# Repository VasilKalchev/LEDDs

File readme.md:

<p align=center>trailing-edge dimmer for LED bulbs</p>

<div align=center>

</div>

**LEDDs** is an open-source hardware, DIY, smart dimmer for 230 V LED bulbs. It is built around the ESP32-C3-12F and is designed to sit on a desk or table, replacing standard inline cord switches.

The project consists of a **PCB**, a **3D-printable chassis**, and a **top plate** designed as a PCB. It runs [ESPHome](https://esphome.io) for integration with Home Assistant and features a **rotary encoder** so it can be controlled easily or used as a standalone device.

> [!CAUTION]
> **MAINS VOLTAGE:** This device operates at **230 VAC**. Touching live components can result in serious injury or death.
> * Only build if you have relevant experience with high-voltage electronics.
> * Always unplug before opening!
> * While the design includes safety features (fuse, MOVs), it is not a certified design and should be treated with caution.

## Table of contents
* [Is this project for you?](#is-this-project-for-you)
* [Why trailing-edge?](#why-trailing-edge)
* [Features](#star-features)
* [Specifications](#straight_ruler-specifications)
* [Release/fabrication of version 2.0](#releasefabrication-of-v20)
* [Repository structure](#open_file_folder-repository-structure)
* [Bill of materials](#euro-bill-of-materials)
* [Build](#hammer-build)
   * [Prerequisites](#prerequisites)
   * [1. Ordering the components](#1-ordering-the-components)
   * [2. PCB assembly instructions](#2-pcb-assembly-instructions)
   * [3. Flashing the firmware](#3-flashing-the-firmware)
   * [4. Preparing the enclosure](#4-preparing-the-enclosure)
   * [5. Final assembly](#5-final-assembly)
* [Usage](#bulb-usage)
   * [Control](#control)
   * [LED indicators](#led-indicators)
   * [Default light effects](#default-light-effects)
* [Versions, releases and compatibility](#page_with_curl-versions-releases-and-compatibility)
* [Contributing](#coffee-contributing)
* [License](#license)

---

## Is this project for you?
This project is suitable if you:
 - have experience with mains-powered electronics
 - want a LED bulbs dimmer for a desk

This project is NOT suitable if you:
 - are new to electronics
 - need a certified wall dimmer

## Why trailing-edge?
Most dimmers use **leading-edge** (TRIAC) dimming (designed for incandescent bulbs). They modulate power to the load by cutting the beginning of the AC half cycle. This creates a voltage spike that can cause buzzing and reduced lifespan in the capacitive power supplies found in LED bulbs.

**LEDDs uses trailing-edge dimming.** By using MOSFETs to cut the waveform at the *end* of the AC cycle, there isn't a positive voltage spike. This results in:
* reduced electrical noise and buzzing
* smoother dimming with reduced flicker
* lower minimum brightness levels

> The schematic and PCB can be viewed in [KiCanvas][kicanvas_v2_0].

## :star: Features
- **ESP32-C3** based with ESPHome firmware for integration with Home Assistant
- **Standalone** operation, doesn't require Home Assistant
- **Rotary encoder** control: rotate to dim, press+rotate for effects, press for on/off
- LEDs: red (rotation feedback), blue (status indicator), white (ambient)
- Included **enclosure design**: 100 mm × 51 mm × 25 mm - ideal for desk lamp modifications
- Low idle power: ~0.3 W
- Open source: MIT licensed

## :straight_ruler: Specifications

| Parameter              | Value                        |
| ---------------------- | ---------------------------- |
| Input voltage          | 230 VAC                      |
| Maximum output power   | 100 W                        |
| Idle power draw        | ~0.3 W                       |
| Protections            | fuse and MOVs                |
| Microcontroller module | ESP32-C3-12F [^1]            |
| Dimensions             | 100 × 51 × 25 mm (W × D × H) |
| Connectivity           | Wi-Fi, USB-C (programming)   |

[^1]: Also compatible with ESP8266 ESP-12F, but not recommended.

> [!IMPORTANT]
> Designed for 230 VAC at 50 Hz.
>
> Usage with 120 VAC at 60 Hz will probably require adjusting the component values of the zero-cross and the voltage regulator circuits.

---

## Release/fabrication of v2.0

> **Status:** Verified working.
> The fabricated board from this release is fully functional. Minor issues may exist but do not affect operation: [/doc/releaselog.md v2.0][releaselog_v2_0].
>
> :memo: **Recommended for fabrication.**

<p align="center">

</p>

---

## :open_file_folder: Repository structure
```

├── hw/                       # main PCB design (KiCad project)
│   ├── lib/                  # symbols and footprints
│   ├── assets/               # fonts and graphics
│   └── export/               # scripts for exporting gerbers, BOM and schematics/PCB PDFs
├── fw/                       # ESPHome YAML configurations and firmware binaries
├── doc/                      # additional documentation
│   ├── releaselog.md         # main PCB release log
│   ├── changelog.md          # main PCB change log
├── enclosure/
│   ├── chassis/              # 3D printable chassis
│   │   ├── releaselog.md     # chassis release log
│   │   ├── changelog.md      # chassis change log
│   │   ├── vX.Y-variant_a/
│   │   └── vX.Y-variant_b/
│   └── top_plate/            # top plate design (KiCad project)
│       ├── releaselog.md     # top plate release log
│       ├── changelog.md      # top plate change log
│       ├── vX.Y-variant_a/
│       └── vX.Y-variant_b/
└── img/                      # photos and renders
```

---

## :euro: Bill of materials
 - components: ~€15
 - PCB: €4 (ordered as prototype board)
 - top plate: €0-4 (can be combined with the main PCB)
 - chassis: €4-10 (when ordered)

Check out the BOM provided in the release bundle for complete components list.

## :hammer: Build

### Overview
Building LEDDs consists of four main steps:
 1. Ordering the PCB, the chassis and the components.
 2. Assembling the PCB.
 3. Flashing and configuring the firmware.
 4. Wiring and final assembly.

### Prerequisites
- skills: soldering [^2], experience with mains electricity
- tools: soldering iron, hot air gun (recommended), 3D printer or access to 3D printing service, multimeter

[^2]: Trickiest part is the USB-C port. The board can be ordered pre-assembled.

Download the [release bundle][dw_release_bundle_v2_0].

### 1. Ordering the components
  - **PCBs**: order the main PCB and the top plate PCB from your preferred fabricator
    - gerbers for JLCPCB: available in the bundle
    - for other fabricators - use KiCad to generate gerbers according to the manufacturer's instructions
  - **chassis**: choose a variant from the provided STL files

### 2. PCB assembly instructions
> [!TIP]
> Use the provided **interactive BOM** ("ibom.html") as a soldering guide.

#### Microcontroller module
<strong>ESP32-C3-12F (recommended)</strong>

- solder R13

<details><summary><strong>ESP8266 ESP-12F (not recommended)</strong></summary>

- insulate pins 12 and 13 from the PCB pads using kapton/electrical tape
- solder JP2
- don't solder R13
- don't solder R6 and D3 ("led_1")
- don't solder R8 and D5 ("led_3")

ESP8266 doesn't support native USB and requires an external USB to serial adapter for programming.

</details>

#### Zero-cross optoisolator
The PCB has footprints for a choice between 2 optoisolators that connect the zero-cross signal to the MCU.

<strong>H11L1SR2M</strong>

 - solder the optoisolator on footprint U4
 - solder C13

<details><summary><strong>PC817XI (not recommended)</strong></summary>

- solder the optoisolator on footprint U3
- no need to solder C13

This optoisolator is the same as the one used for controlling the MOSFET's gate, but didn't work well for the zero-cross circuit.

</details>

#### Skipping the relay
The relay is used to power off the mains part of the circuit when the load is turned off. This is intended as a peace of mind feature and can be omitted.

 - use a wire to short pin 11 to 14
 - use a wire to short pin 21 to 24
 - no need to solder C3, D2, R2 and Q1

#### Skipping the rotary encoder

If the rotary encoder is not required - solder a push button (SW2) so boot mode can be entered manually.

 - no need to solder R3, R4, C4, C5 and C6

A modified top plate (without a hole in the middle) is recommended for safety reasons (not currently available).

#### Using the UART header instead of the USB for programming *(not tested)*

 - solder R12
 - solder header J4
 - no need to solder R9 and R10

Use a USB to serial adapter.

### 3. Flashing the firmware
 - Connect to the board via USB-C.
 - Use [ESPHome's web flasher](https://web.esphome.io/) to upload one of the provided firmware binaries.
   - hass.bin: Home Assistant + rotary encoder
   - web_server.bin: self hosted web server + rotary encoder
   - standalone: rotary encoder only
 - Set your Wi-Fi credentials using the ESPHome web flasher.
 - Test before wiring.

> [!TIP]
> The YAML configurations of the provided binaries are available under [/fw/esphome/yaml/](/fw/esphome/yaml/).

### 4. Preparing the enclosure
- plastic chassis: install the heat-set threaded inserts in the holes using a soldering iron
- resin chassis: no preparation needed

### 5. Final assembly
 - Mount a knob to the rotary encoder.
 - Place the PCB inside the chassis.
 - Screw the mains power cable to the terminal on the left (marked with a power plug). **Don't connect power until fully assembled.**
 - Screw the lamp socket cable to the terminal on the right (marked with a bulb).
 - Pass the screws through the top plate and place the spacers on the screws.
 - Screw the top plate through the PCB into the chassis.

## :bulb: Usage
### Control
**Directly** *(possible with all firmware variants)*:
 - **press**: on/off
 - **rotate**: brightness adjustment
 - **press + rotate**: cycle lighting effects

**Home Assistant** *(included in hass.bin)*:

Integrating the device in Home Assistant: https://esphome.io/guides/getting_started_hassio/#connecting-your-device-to-home-assistant.

The "Configuration" section allows customization of the device:
 - **Bulb power rating**: input the power rating of the bulb, this is used for the power estimation sensor ("Power \[est\]").
 - **Gamma correct**: Adjust the dimming curve to appear linear to the human eye.
 - **Minimum level**: The lowest level at which the bulb emits light. *Note: this value needs to be updated every time gamma correction is changed.*
 - **Restore mode**: Initial state of the bulb when powered.
 - **Transition length**: How fast the bulb changes brightness in milliseconds.
 - **LED: red/blue/white**: set the ambient brightness of the LEDs.

**Web server** *(included in web_server.bin)*:
> This is useful if you don't have Home Assistant, but want to control the device remotely.

### LED indicators
There are three LEDs on the board:
 - **red (top, led_1):** ambient / rotation feedback
 - **blue (top, led_2):** ambient / status indicator
 - **white (bottom, led_3):** ambient

### Default light effects
Light effects can be cycled with the rotary encoder or chosen directly from a UI.

 - Pulse (low, fast)
 - Pulse (low, slow)
 - Pulse (high, fast)
 - Pulse (high, slow)
 - Pulse (full, fast)
 - Pulse (full, slow)
 - Flicker (soft)
 - Flicker (intense)

<!--
<div>

</div>
-->

## :page_with_curl: Versions, releases and compatibility
Each fabrication run results in a **GitHub release**.
- Semantic versioning (major.minor), no patch versions.
- PCB, chassis, and top plate are versioned independently.
- Same **major versions fit together**.

## :coffee: Contributing
Every type of contribution is welcome, like improvements or corrections to the:
- schematic/PCB design
- documentation
- enclosure (chassis and top panel) design
- ESPHome configuration

Contributions can be made as improvements or as variants (e.g. different enclosure design, ESPHome configuration, etc.).

```mermaid
gitGraph
    commit tag: "v1.0"
    branch improve_x
    checkout improve_x
    commit id: "Improve x"
    commit id: "Re-generate exports"
    commit id: "Update board documentation"
    checkout main
    merge improve_x tag: "v1.1"
    branch replace_y
    checkout replace_y
    commit id: "Replace y"
    commit id: "Generate exports"
    commit id: "Compile binaries"
    commit id: "Update all documentation"
    checkout main
    merge replace_y tag: "v2.0"
```

You're welcome to post your builds in [Discussions: Show and tell](https://github.com/VasilKalchev/LEDDs/discussions/categories/show-and-tell).

## License
This project is licensed under the **MIT License**.

---

**Disclaimer**: This project involves mains voltage electricity. The author assumes no liability for injury, damage, or regulatory violations. Build and use at your own risk. Ensure compliance with local electrical codes and regulations.

<!-- current version links -->

[kicanvas_v2_0]: https://kicanvas.org/?github=https%3A%2F%2Fgithub.com%2FVasilKalchev%2FLEDDs%2Ftree%2Fv2.0%2Fhw
[dw_release_bundle_v2_0]: https://github.com/VasilKalchev/LEDDs/releases/download/v2.0/LEDDs.v2.0.zip

[releaselog_v2_0]: /doc/releaselog.md#v20---2025-04-02

<!-- /current version links -->

<!-- checklist
<details>
<summary>/readme.md checklist</summary>

 - [x] set release result (template in releaselog.md)
 - [x] update the sections as needed
 - [x] comment out this checklist

</details>

-->
<!-- /checklist -->

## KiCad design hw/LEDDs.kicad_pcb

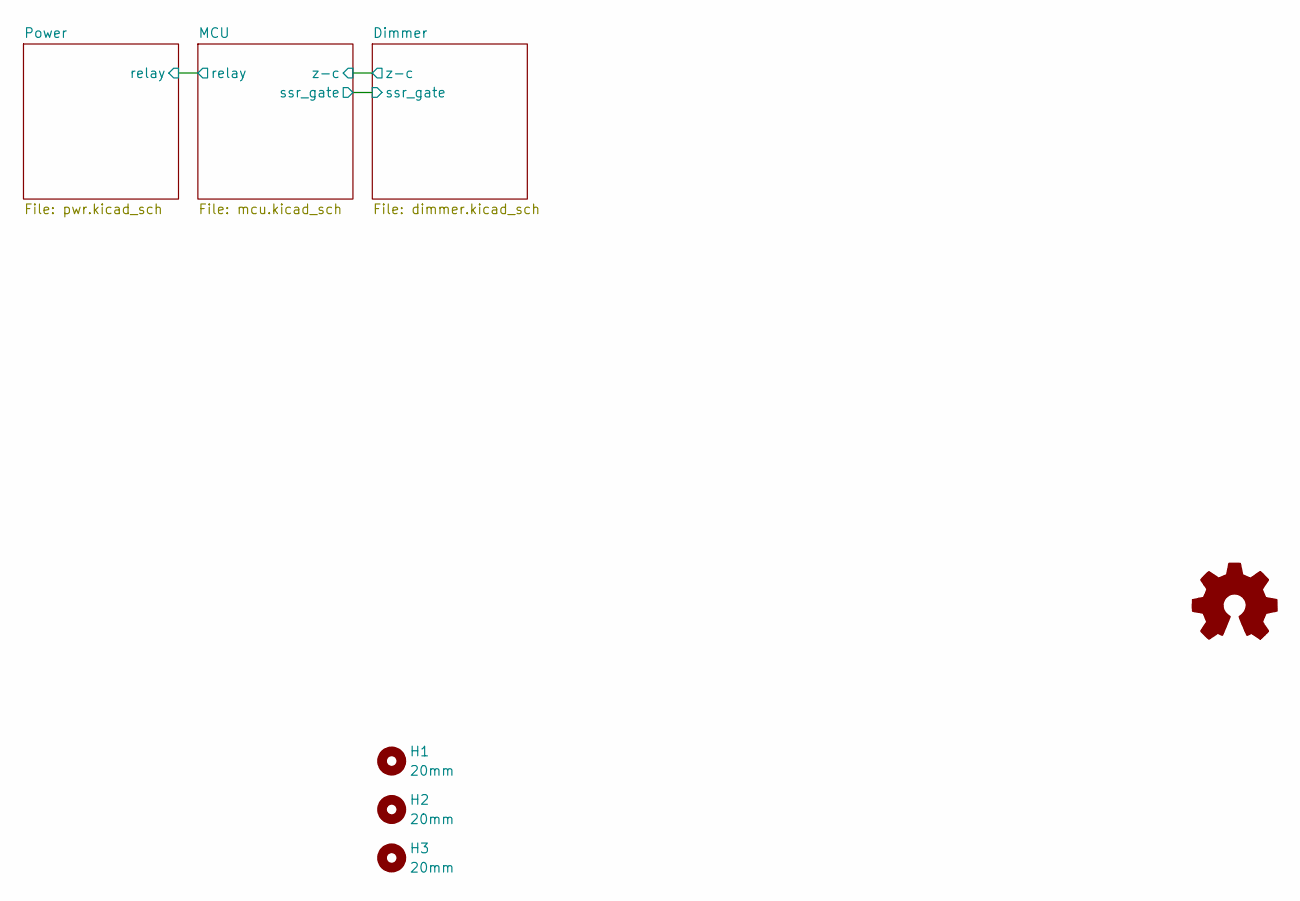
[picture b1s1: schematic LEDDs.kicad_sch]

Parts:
H1, H2, H3: 20mm; MountingHole_3.2mm_M3_DIN965_Pad_TopBottom

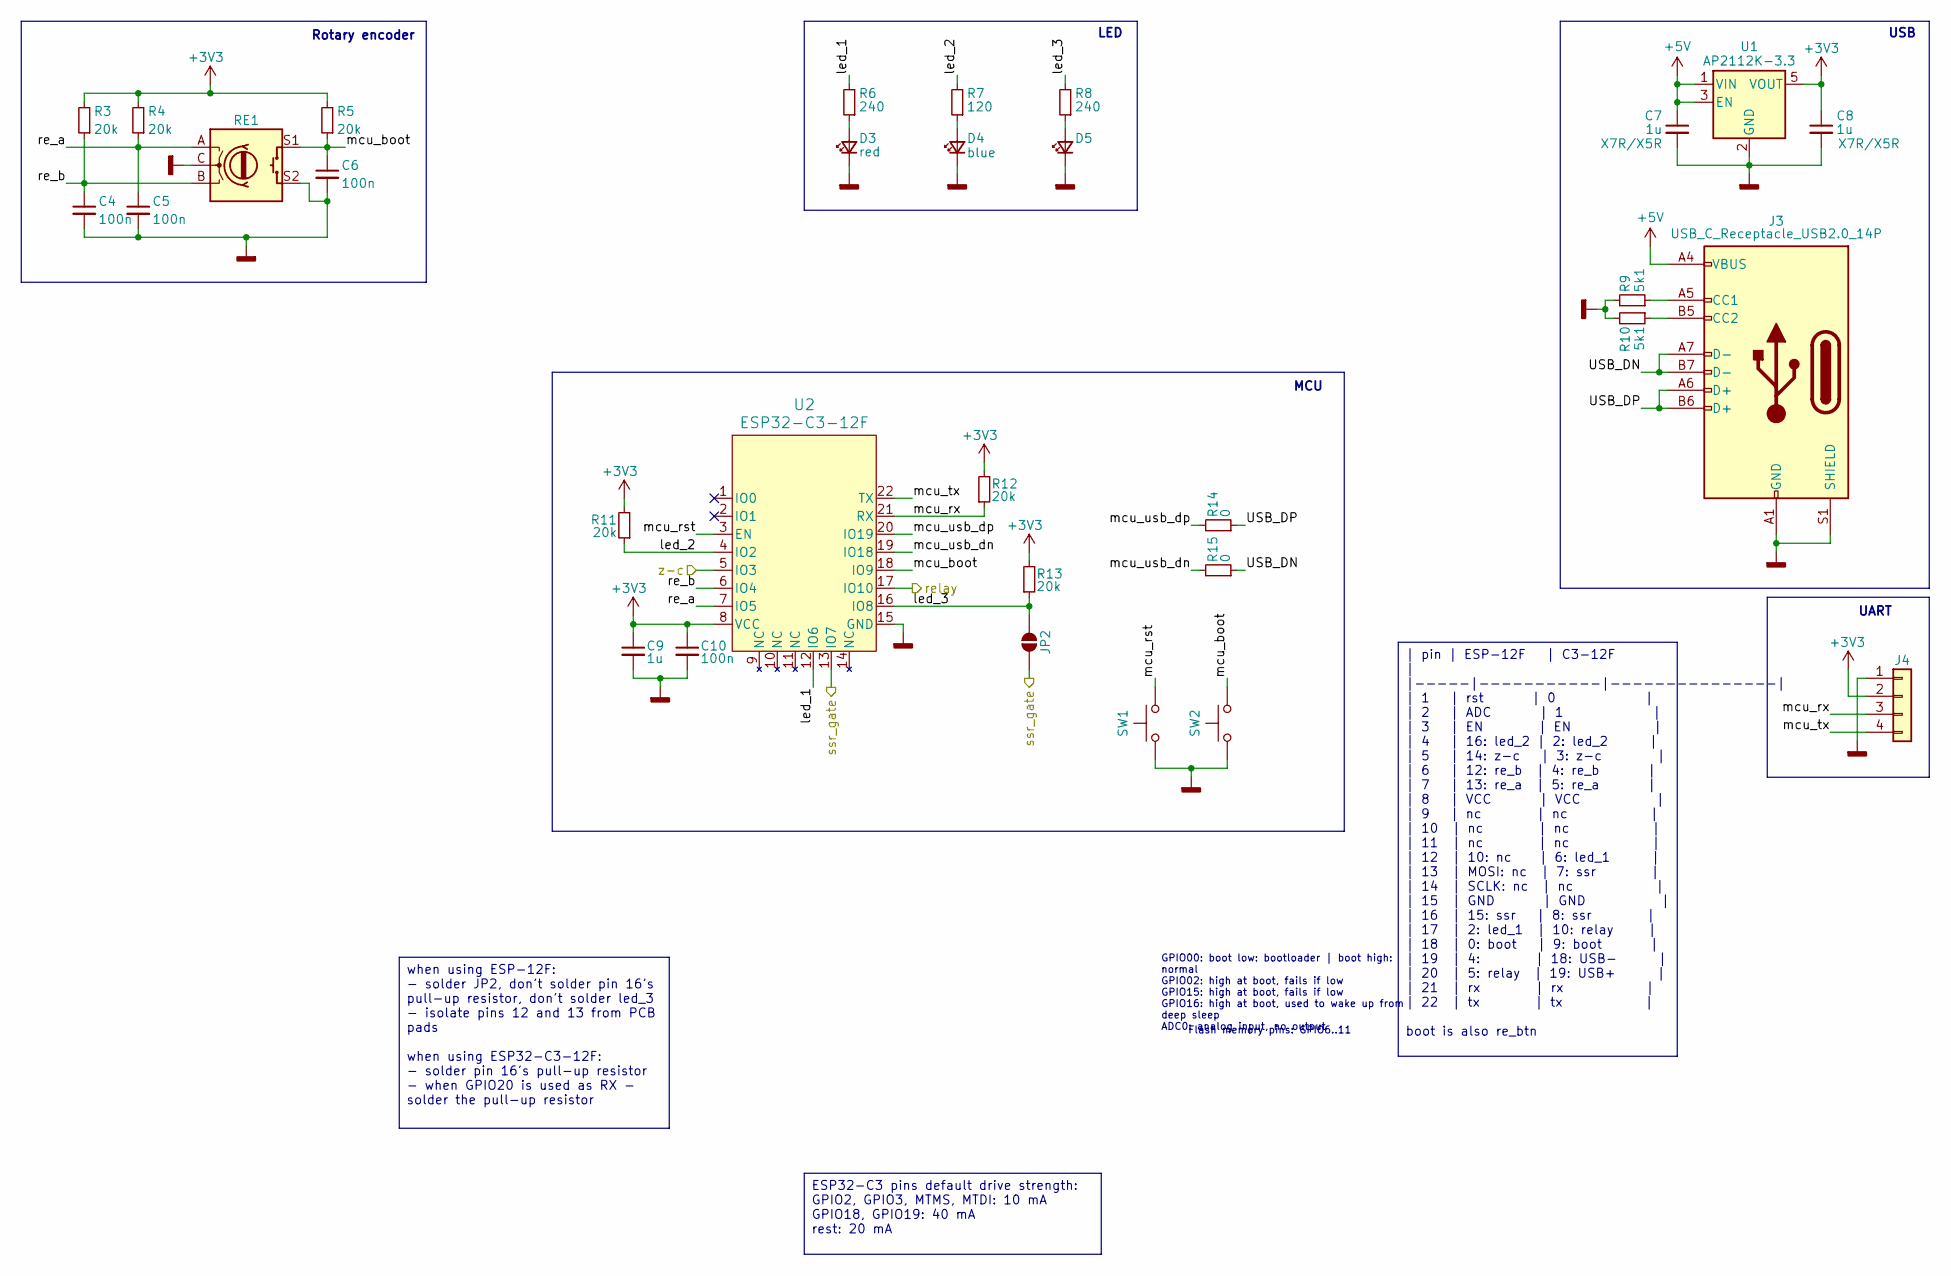
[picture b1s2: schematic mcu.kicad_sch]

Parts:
C4, C5, C6, C10: 100n; C_0805_2012Metric_Pad1.18x1.45mm_HandSolder
C7, C8, C9: 1u; C_0805_2012Metric_Pad1.18x1.45mm_HandSolder
D3: red; LED_0805_2012Metric_Pad1.15x1.40mm_HandSolder
D4: blue; LED_0805_2012Metric_Pad1.15x1.40mm_HandSolder
D5: LED_0805_2012Metric_Pad1.15x1.40mm_HandSolder
J3: USB_C_Receptacle_USB2.0_14P; USB_C_Receptacle_GCT_USB4110
J4: Conn_01x06; PinHeader_1x04_P2.54mm_Vertical
JP2: SolderJumper_2_Open; SolderJumper-2_P1.3mm_Open_RoundedPad1.0x1.5mm
R3, R4, R5, R11, R12, R13: 20k; R_0805_2012Metric_Pad1.20x1.40mm_HandSolder
R6, R8: 240; R_0805_2012Metric_Pad1.20x1.40mm_HandSolder
R7: 120; R_0805_2012Metric_Pad1.20x1.40mm_HandSolder
R9, R10: 5k1; R_0805_2012Metric_Pad1.20x1.40mm_HandSolder
R14, R15: 0; R_0805_2012Metric_Pad1.20x1.40mm_HandSolder
RE1: RotaryEncoder_Switch; RotaryEncoder_Alps_EC11E-Switch_Vertical_H20mm
SW1, SW2: SW_Push_SPST_NO_Alps_SKRK
U1: AP2112K-3.3; SOT-23-5
U2: ESP32-C3-12F; ESP32-C3-12F_RFS

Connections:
+3V3: C8.1, C9.1, C10.1, J4.2, R3.2, R4.2, R5.2, R11.2, R12.2, R13.2, U1.5 (VOUT), U2.8 (VCC); also elsewhere on the board
+5V: C7.1, J3.A4 (VBUS), J3.A9 (VBUS), J3.B4 (VBUS), J3.B9 (VBUS), U1.1 (VIN), U1.3 (EN)
/Dimmer/ssr_gate: JP2.2 (B), U2.13 (IO7); also elsewhere on the board
/Dimmer/z-c: U2.5 (IO3); also elsewhere on the board
/MCU/USB_DN: J3.A7 (D-), J3.B7 (D-), R15.1
/MCU/USB_DP: J3.A6 (D+), J3.B6 (D+), R14.1
/MCU/led_1: R6.2, U2.12 (IO6)
/MCU/led_2: R7.2, R11.1, U2.4 (IO2)
/MCU/led_3: JP2.1 (A), R8.2, R13.1, U2.16 (IO8)
/MCU/mcu_boot: C6.1, R5.1, RE1.S1, SW2.2, U2.18 (IO9)
/MCU/mcu_rst: SW1.2, U2.3 (EN)
/MCU/mcu_rx: J4.3, R12.1, U2.21 (RX)
/MCU/mcu_tx: J4.4, U2.22 (TX)
/MCU/mcu_usb_dn: R15.2, U2.19 (IO18)
/MCU/mcu_usb_dp: R14.2, U2.20 (IO19)
/MCU/re_a: C5.1, R4.1, RE1.A, U2.7 (IO5)
/MCU/re_b: C4.1, R3.1, RE1.B, U2.6 (IO4)
/MCU/relay: U2.17 (IO10); also elsewhere on the board
GNDD: C4.2, C5.2, C6.2, C7.2, C8.2, C9.2, C10.2, D3.1 (K), D4.1 (K), D5.1 (K), J3.A1 (GND), J3.A12 (GND), J3.B1 (GND), J3.B12 (GND), J3.S1 (SHIELD), J4.1, R9.2, R10.2, RE1.C, RE1.S2, SW1.1, SW2.1, U1.2 (GND), U2.15 (GND); also elsewhere on the board
unnamed: D3.2 (A), R6.1
unnamed: D4.2 (A), R7.1
unnamed: D5.2 (A), R8.1
unnamed: J3.A5 (CC1), R9.1
unnamed: J3.B5 (CC2), R10.1

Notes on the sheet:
MCU
| pin | ESP-12F | C3-12F | |-----|-----------|---------------| | 1 | rst | 0 | | 2 | ADC | 1 | | 3 | EN | EN | | 4 | 16: led_2 | 2: led_2 | | 5 | 14: z-c | 3: z-c | | 6 | 12: re_b | 4: re_b | | 7 | 13: re_a | 5: re_a | | 8 | VCC | VCC | | 9 | nc | nc | | 10 | nc | nc | | 11 | nc | nc | | 12 | 10: n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
USB
ESP32-C3 pins default drive strength: GPIO2, GPIO3, MTMS, MTDI: 10 mA GPIO18, GPIO19: 40 mA rest: 20 mA
when using ESP-12F: - solder JP2, don't solder pin 16's pull-up resistor, don't solder led_3 - isolate pins 12 and 13 from PCB pads when using ESP32-C3-12F: - solder pin 16's pull-up resistor - when GPIO20 is used as RX - solder the pull-up resistor
Rotary encoder
GPIO00: boot low: bootloader | boot high: normal GPIO02: high at boot, fails if low GPIO15: high at boot, fails if low GPIO16: high at boot, used to wake up from deep sleep ADC0: analog input, no output
Flash memory pins: GPIO6..11
LED
UART

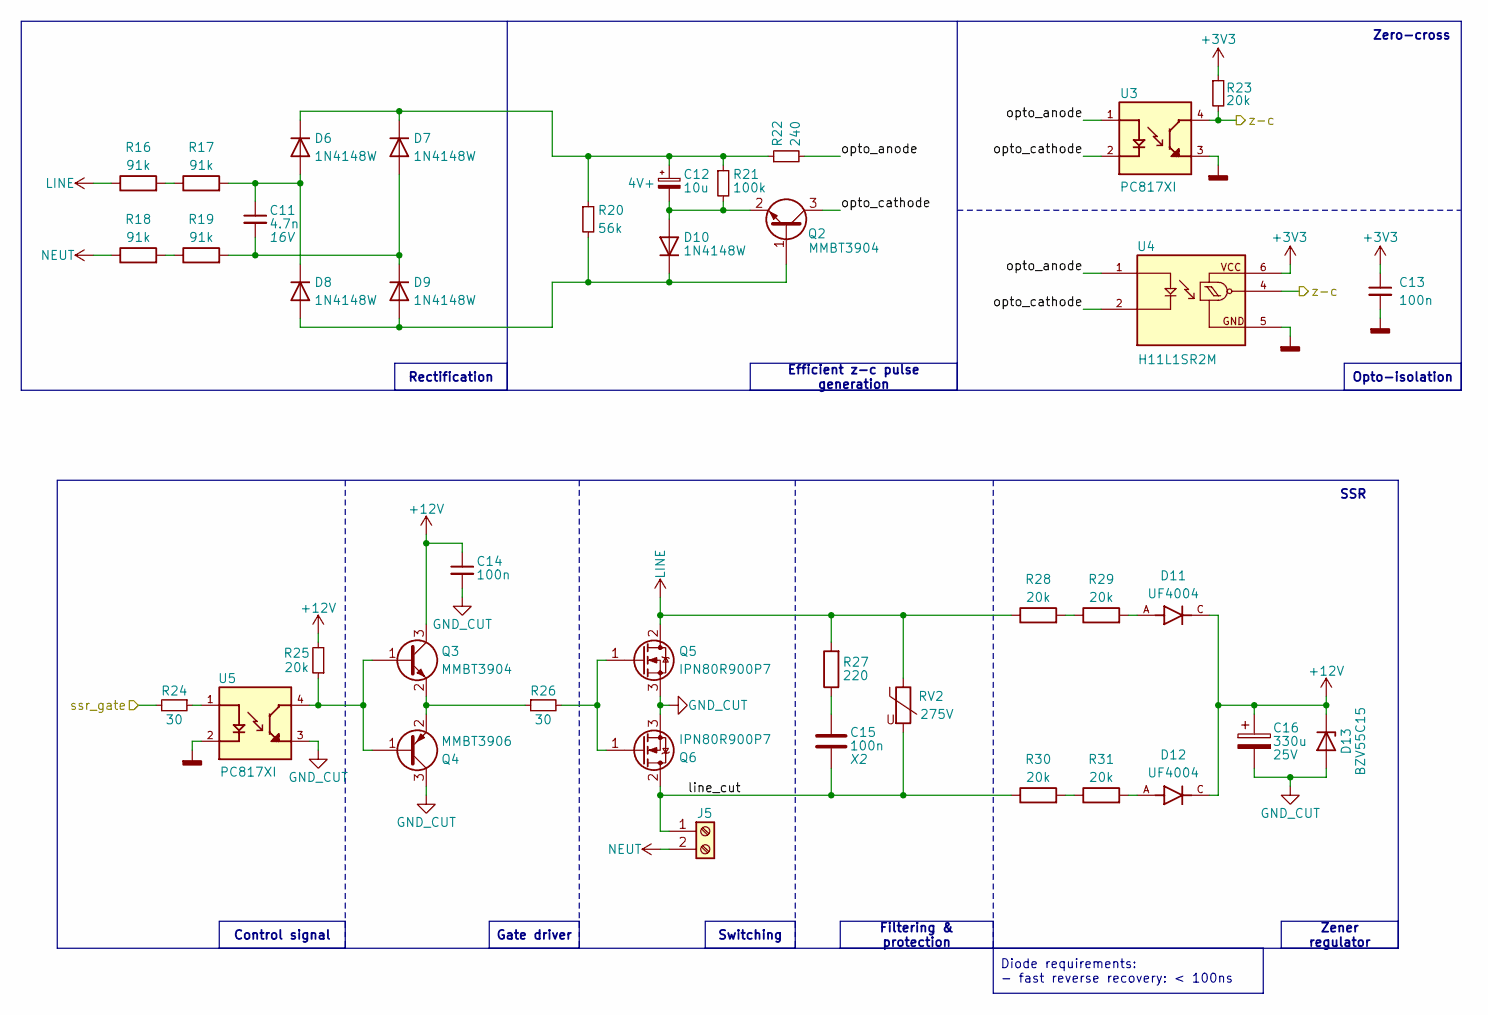
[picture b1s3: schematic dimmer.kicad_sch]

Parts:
C11: 4.7n; C_1206_3216Metric_Pad1.33x1.80mm_HandSolder
C12: 10u; CP_Elec_5x5.7
C13, C14: 100n; C_0805_2012Metric_Pad1.18x1.45mm_HandSolder
C15: 100n; C_Rect_L13.0mm_W6.0mm_P10.00mm_FKS3_FKP3_MKS4
C16: 330u; CP_Elec_8x10
D6, D7, D8, D9, D10: 1N4148W; D_SOD-123
D11, D12: UF4004; DIOAD1055W87L533D272; PARTREV N/A
D13: BZV55C15; D_DO-41_SOD81_P7.62mm_Horizontal
J5: Screw_Terminal_01x02; TerminalBlock_bornier-2_P5.08mm
Q2, Q3: MMBT3904; SOT-23
Q4: MMBT3906; SOT-23
Q5, Q6: IPN80R900P7; SOT-223-3_TabPin2
R16, R17, R18, R19: 91k; R_1206_3216Metric_Pad1.30x1.75mm_HandSolder
R20: 56k; R_0805_2012Metric_Pad1.20x1.40mm_HandSolder
R21: 100k; R_0805_2012Metric_Pad1.20x1.40mm_HandSolder
R22: 240; R_0805_2012Metric_Pad1.20x1.40mm_HandSolder
R23, R25: 20k; R_0805_2012Metric_Pad1.20x1.40mm_HandSolder
R24, R26: 30; R_0805_2012Metric_Pad1.20x1.40mm_HandSolder
R27: 220; R_1206_3216Metric_Pad1.30x1.75mm_HandSolder
R28, R29, R30, R31: 20k; R_1206_3216Metric_Pad1.30x1.75mm_HandSolder
RV2: 275V; RV_Disc_D9mm_W3.5mm_P5mm
U3, U5: PC817XI; SOIC254P975X460-4N
U4: H11L1SR2M; IC_H11L1SR2M; PARTREV 3

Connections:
+3V3: C13.1, R23.1, U4.6; also elsewhere on the board
+12V: C14.1, C16.1, D11.C, D12.C, D13.1 (K), Q3.3 (C), R25.2
/Dimmer/line_cut: C15.2, J5.1, Q6.2 (D), R30.1, RV2.2
/Dimmer/opto_anode: R22.2, U3.1, U4.1
/Dimmer/opto_cathode: Q2.3 (C), U3.2, U4.2
/Dimmer/ssr_gate: R24.2; also elsewhere on the board
/Dimmer/z-c: R23.2, U3.4, U4.4; also elsewhere on the board
GNDD: C13.2, U3.3, U4.5, U5.2; also elsewhere on the board
GND_CUT: C14.2, C16.2, D13.2 (A), Q4.3 (C), Q5.3 (S), Q6.3 (S), U5.3
LINE: Q5.2 (D), R16.1, R27.2, R28.1, RV2.1; also elsewhere on the board
NEUT: J5.2, R18.1; also elsewhere on the board
unnamed: C15.1, R27.1
unnamed: C11.1, D6.2 (A), D8.1 (K), R17.2
unnamed: C12.1, D6.1 (K), D7.1 (K), R20.1, R21.1, R22.1
unnamed: C11.2, D7.2 (A), D9.1 (K), R19.2
unnamed: C12.2, D10.2 (A), Q2.2 (E), R21.2
unnamed: D8.2 (A), D9.2 (A), D10.1 (K), Q2.1 (B), R20.2
unnamed: D11.A, R29.2
unnamed: D12.A, R31.2
unnamed: Q3.1 (B), Q4.1 (B), R25.1, U5.4
unnamed: Q3.2 (E), Q4.2 (E), R26.1
unnamed: Q5.1 (G), Q6.1 (G), R26.2
unnamed: R16.2, R17.1
unnamed: R18.2, R19.1
unnamed: R24.1, U5.1
unnamed: R28.2, R29.1
unnamed: R30.2, R31.1

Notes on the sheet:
Control signal
Filtering & protection
SSR
Switching
Diode requirements: - fast reverse recovery: < 100ns
Rectification
Efficient z-c pulse generation
Gate driver
Zener regulator
Opto-isolation
Zero-cross

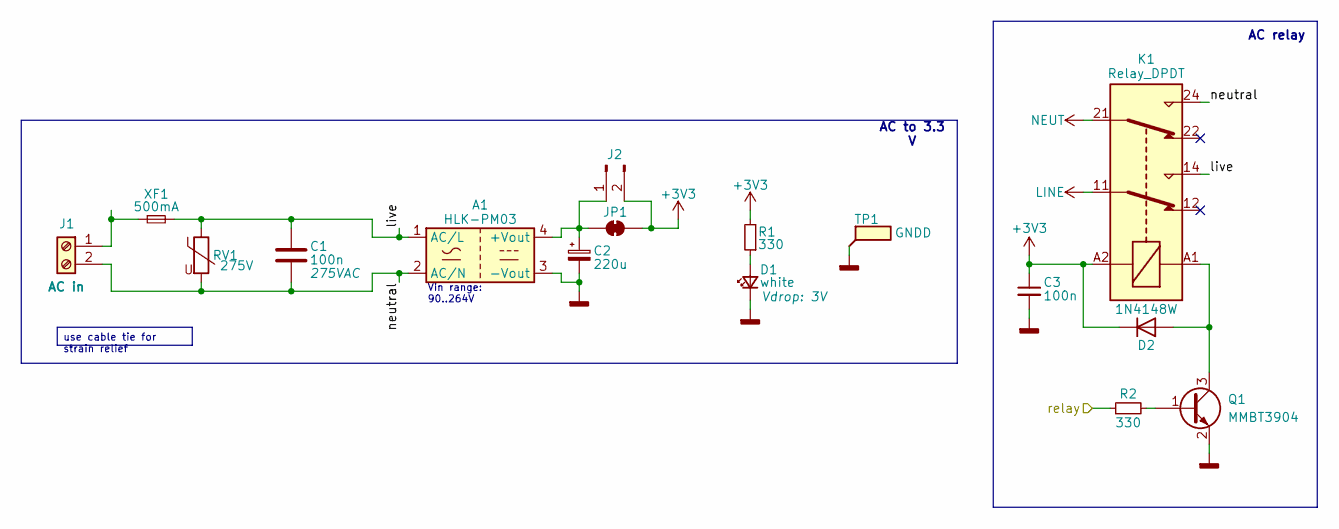
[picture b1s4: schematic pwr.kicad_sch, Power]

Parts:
A1: HLK-PM03; Converter_ACDC_Hi-Link_HLK-PMxx
C1: 100n; C_Rect_L13.0mm_W6.0mm_P10.00mm_FKS3_FKP3_MKS4
C2: 220u; CP_Elec_8x6.5
C3: 100n; C_0805_2012Metric_Pad1.18x1.45mm_HandSolder
D1: white; LED_0805_2012Metric_Pad1.15x1.40mm_HandSolder
D2: 1N4148W; D_SOD-123
J1: Screw_Terminal_01x02; TerminalBlock_bornier-2_P5.08mm
J2: Conn_01x02_Pin; PinSocket_1x02_P2.54mm_Vertical
JP1: SolderJumper_2_Bridged; SolderJumper-2_P1.3mm_Bridged_RoundedPad1.0x1.5mm
K1: Relay_DPDT; HK19F
Q1: MMBT3904; SOT-23
R1, R2: 330; R_0805_2012Metric_Pad1.20x1.40mm_HandSolder
RV1: 275V; RV_Disc_D9mm_W3.5mm_P5mm
TP1: GNDD; TestPoint_Pad_D1.0mm
XF1: 500mA; Fuse_Schurter_UMZ250

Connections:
+3V3: C3.1, D2.1 (K), J2.2, JP1.2 (B), K1.A2, R1.2; also elsewhere on the board
/MCU/relay: R2.1; also elsewhere on the board
/Power/live: A1.1 (AC/L), C1.1, K1.14, RV1.1, XF1.2
/Power/neutral: A1.2 (AC/N), C1.2, J1.2, K1.24, RV1.2
GNDD: A1.3 (-Vout), C2.2, C3.2, D1.1 (K), Q1.2 (E), TP1.1; also elsewhere on the board
LINE: K1.11; also elsewhere on the board
NEUT: K1.21; also elsewhere on the board
unnamed: A1.4 (+Vout), C2.1, J2.1, JP1.1 (A)
unnamed: D1.2 (A), R1.1
unnamed: D2.2 (A), K1.A1, Q1.3 (C)
unnamed: J1.1, XF1.1
unnamed: Q1.1 (B), R2.2

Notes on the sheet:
AC relay
use cable tie for strain relief
AC to 3.3 V
Vin range: 90..264V

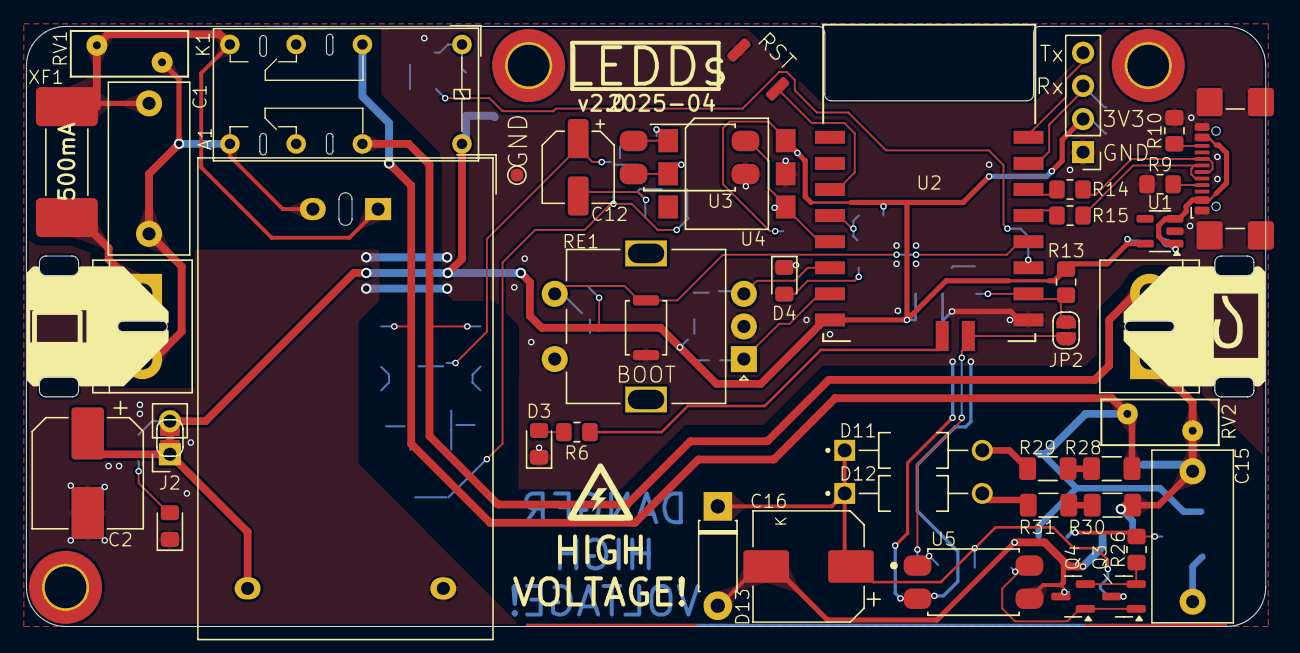
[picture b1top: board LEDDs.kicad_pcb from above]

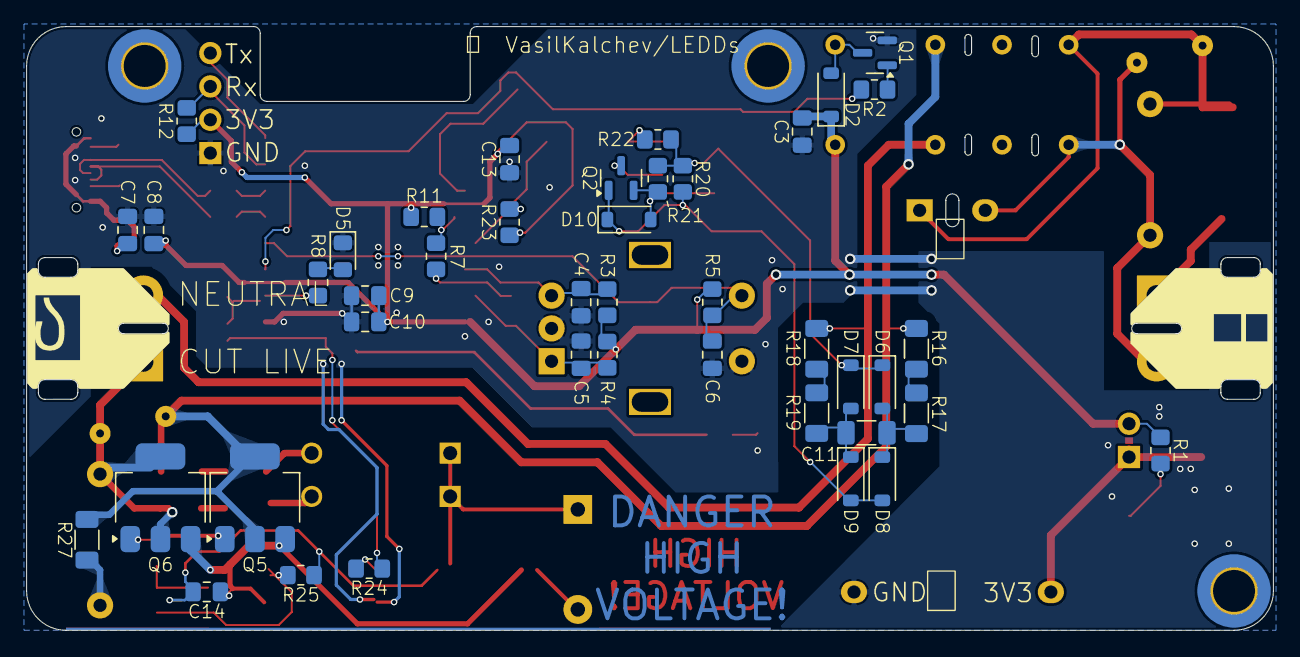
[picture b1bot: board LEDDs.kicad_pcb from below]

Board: 2 copper layers, 95.0 x 46.0 mm, 91 parts (42 on the bottom side), 54 nets.

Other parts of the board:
SS1: high voltage sign; LOGO

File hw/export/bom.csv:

"Reference","Value","Footprint","Description","Qty","DNP"
"A1","HLK-PM03","Converter_ACDC:Converter_ACDC_Hi-Link_HLK-PMxx","","1",""
"C1,C3,C4,C5,C6,C10,C13,C14,C15","100n","Capacitor_SMD:C_0805_2012Metric_Pad1.18x1.45mm_HandSolder,Capacitor_THT:C_Rect_L13.0mm_W6.0mm_P10.00mm_FKS3_FKP3_MKS4","","9",""
"C2","220u","Capacitor_SMD:CP_Elec_8x6.5","","1",""
"C7,C8,C9","1u","Capacitor_SMD:C_0805_2012Metric_Pad1.18x1.45mm_HandSolder","Unpolarized capacitor, small symbol","3",""
"C11","4.7n","Capacitor_SMD:C_1206_3216Metric_Pad1.33x1.80mm_HandSolder","","1",""
"C12","10u","Capacitor_SMD:CP_Elec_5x5.7","","1",""
"C16","330u","Capacitor_SMD:CP_Elec_8x10","","1",""
"D1","white","LED_SMD:LED_0805_2012Metric_Pad1.15x1.40mm_HandSolder","","1",""
"D2,D6,D7,D8,D9,D10","1N4148W","Diode_SMD:D_SOD-123","","6",""
"D3","red","LED_SMD:LED_0805_2012Metric_Pad1.15x1.40mm_HandSolder","","1",""
"D4","blue","LED_SMD:LED_0805_2012Metric_Pad1.15x1.40mm_HandSolder","","1",""
"D5,SW1,SW2","~","Button_Switch_SMD:SW_Push_SPST_NO_Alps_SKRK,LED_SMD:LED_0805_2012Metric_Pad1.15x1.40mm_HandSolder","Push button switch, generic, two pins","3",""
"D11,D12","UF4004","UF4004:DIOAD1055W87L533D272","","2",""
"D13","BZV55C15","Diode_THT:D_DO-41_SOD81_P7.62mm_Horizontal","","1",""
"H1,H2,H3","20mm","MountingHole:MountingHole_3.2mm_M3_DIN965_Pad_TopBottom","M3x20mm","3",""
"J1,J5","Screw_Terminal_01x02","TerminalBlock:TerminalBlock_bornier-2_P5.08mm","","2",""
"J2","Conn_01x02_Pin","Connector_PinSocket_2.54mm:PinSocket_1x02_P2.54mm_Vertical","Generic connector, single row, 01x02, script generated","1",""
"J3","USB_C_Receptacle_USB2.0_14P","Connector_USB:USB_C_Receptacle_GCT_USB4110","USB 2.0-only 14P Type-C Receptacle connector","1",""
"J4","Conn_01x06","Connector_PinHeader_2.54mm:PinHeader_1x04_P2.54mm_Vertical","Generic connector, single row, 01x04, script generated (kicad-library-utils/schlib/autogen/connector/)","1",""
"K1","Relay_DPDT","Relay:HK19F","","1",""
"KN1","20 mm","","Knob: 20 mm","1",""
"Q1,Q2,Q3","MMBT3904","Package_TO_SOT_SMD:SOT-23","0.2A Ic, 40V Vce, Small Signal NPN Transistor, SOT-23","3",""
"Q4","MMBT3906","Package_TO_SOT_SMD:SOT-23","-0.2A Ic, -40V Vce, Small Signal PNP Transistor, SOT-23","1",""
"Q5,Q6","IPN80R900P7","Package_TO_SOT_SMD:SOT-223-3_TabPin2","N-MOSFET transistor, gate/drain/source","2",""
"R1,R2","330","Resistor_SMD:R_0805_2012Metric_Pad1.20x1.40mm_HandSolder","","2",""
"R3,R4,R5,R11,R12,R13,R23,R25,R28,R29,R30,R31","20k","Resistor_SMD:R_0805_2012Metric_Pad1.20x1.40mm_HandSolder,Resistor_SMD:R_1206_3216Metric_Pad1.30x1.75mm_HandSolder","","12",""
"R6,R8,R22","240","Resistor_SMD:R_0805_2012Metric_Pad1.20x1.40mm_HandSolder","","3",""
"R7","120","Resistor_SMD:R_0805_2012Metric_Pad1.20x1.40mm_HandSolder","","1",""
"R9,R10","5k1","Resistor_SMD:R_0805_2012Metric_Pad1.20x1.40mm_HandSolder","Resistor, small symbol","2",""
"R14,R15","0","Resistor_SMD:R_0805_2012Metric_Pad1.20x1.40mm_HandSolder","","2",""
"R16,R17,R18,R19","91k","Resistor_SMD:R_1206_3216Metric_Pad1.30x1.75mm_HandSolder","","4",""
"R20","56k","Resistor_SMD:R_0805_2012Metric_Pad1.20x1.40mm_HandSolder","","1",""
"R21","100k","Resistor_SMD:R_0805_2012Metric_Pad1.20x1.40mm_HandSolder","","1",""
"R24,R26","30","Resistor_SMD:R_0805_2012Metric_Pad1.20x1.40mm_HandSolder","","2",""
"R27","220","Resistor_SMD:R_1206_3216Metric_Pad1.30x1.75mm_HandSolder","","1",""
"RE1","RotaryEncoder_Switch","Rotary_Encoder:RotaryEncoder_Alps_EC11E-Switch_Vertical_H20mm","","1",""
"RV1,RV2","275V","Varistor:RV_Disc_D9mm_W3.5mm_P5mm","","2",""
"SP1,SP2,SP3","15mm","","Spacer: M3x15mm","3",""
"TI1,TI2,TI3","4x4.2 mm","","Threaded insert: M3 x L4 x OD4.2 mm","3",""
"U1","AP2112K-3.3","Package_TO_SOT_SMD:SOT-23-5","600mA low dropout linear regulator, with enable pin, 3.8V-6V input voltage range, 3.3V fixed positive output, SOT-23-5","1",""
"U2","ESP32-C3-12F","ESP32-C3-12F_RFS","","1",""
"U3,U5","PC817XI","PC817XI:SOIC254P975X460-4N","","2",""
"U4","H11L1SR2M","H11L1SR2M:IC_H11L1SR2M","","1",""
"XF1","500mA","Fuse:Fuse_Schurter_UMZ250","Fuse, small symbol","1",""

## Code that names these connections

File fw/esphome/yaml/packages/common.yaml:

substitutions:
  device_friendly_name: "LEDDs 2"

  # user configuration
  dim_step: 6.25  # 10 % | 6.25 %
  gamma_correct: 2.2
  minimum_level: 15 %
  restore_mode: ALWAYS_OFF  # ALWAYS_OFF | ALWAYS_ON
  transition_length: 300 ms
  feedback_blink_length: 40 ms

  # IDs
  light_id: dimmer_light
  ac_dimmer_id: ac_dimmer_output
  rotary_encoder_id: rotary_encoder_sensor
  rotary_encoder_btn_id: rotary_encoder_btn_sensor
  feedback_led_id: red_led

  # pinout
  led_2_pin: GPIO2
  zc_pin: GPIO3
  re_b_pin: GPIO4
  re_a_pin: GPIO5
  led_1_pin: GPIO6
  gate_pin: GPIO7
  led_3_pin: GPIO8
  re_btn_pin: GPIO9
  relay_pin: GPIO10

# =====

esp32:
  variant: esp32c3
  framework:
    type: esp-idf
    version: recommended

logger:
    level: WARN  # NONE < ERROR < WARN < INFO < DEBUG < VERBOSE < VERY_VERBOSE

wifi:
  ap:

captive_portal:

improv_serial:
  next_url: https://github.com/VasilKalchev/LEDDs/tree/v2.0

ota:
  platform: esphome
  on_begin:
    then:
      - output.turn_off:
          id: ${ac_dimmer_id}

# =====

light:
  - platform: monochromatic
    id: ${light_id}
    name: "Bulb"
    output: ${ac_dimmer_id}
    icon: "mdi:lightbulb-variant"
    default_transition_length: ${transition_length}
    gamma_correct: ${gamma_correct}
    restore_mode: ${restore_mode}
    effects: !include monochromic_effects.yaml

  - platform: monochromatic
    id: red_led
    name: "LED: red"
    output: led1
    icon: "mdi:led-outline"
    entity_category: "config"
    default_transition_length: 1000 ms
    restore_mode: RESTORE_DEFAULT_ON
    initial_state:
      state: on
      brightness: 100 %

  - platform: monochromatic
    id: blue_led
    name: "LED: blue"
    output: led2
    icon: "mdi:led-outline"
    entity_category: "config"
    default_transition_length: 1000 ms
    restore_mode: RESTORE_DEFAULT_ON
    initial_state:
      state: on
      brightness: 100 %

  - platform: monochromatic
    id: white_led
    name: "LED: white"
    output: led3
    icon: "mdi:led-outline"
    entity_category: "config"
    default_transition_length: 1000 ms
    restore_mode: RESTORE_DEFAULT_ON
    initial_state:
      state: on
      brightness: 100 %


  - platform: status_led
    id: blue_status_led
    pin:
      number: ${led_1_pin}
      allow_other_uses: true


sensor:
  - platform: rotary_encoder
    id: ${rotary_encoder_id}
    name: "Knob"
    icon: "mdi:knob"
    internal: true
    pin_a: ${re_a_pin}
    pin_b: ${re_b_pin}
    min_value: -1
    max_value: 1
    publish_initial_value: true
    restore_mode: ALWAYS_ZERO
    filters:
      - debounce: 20 ms
    on_clockwise:
      then:
        - if:
            condition:
              - binary_sensor.is_off: ${rotary_encoder_btn_id}
            then:
              - script.execute:
                  id: feedback_blink
                  condition: !lambda 'return id(${light_id}).remote_values.get_brightness() < 1.0;'
              - light.dim_relative:
                  id: ${light_id}
                  relative_brightness: ${dim_step} %
                  transition_length: 0 ms
            else:
              - script.execute:
                  id: feedback_blink
                  condition: !lambda 'return id(${light_id}).get_current_effect_index() < (uint32_t)id(${light_id}).get_effect_count();'
              - script.execute:
                  id: walk_effects
                  forward: true

    on_anticlockwise:
      then:
        - if:
            condition:
              - binary_sensor.is_off: ${rotary_encoder_btn_id}
            then:
              - script.execute:
                  id: feedback_blink
                  condition: !lambda 'return id(${light_id}).remote_values.get_state() > 0.0;'
              - light.dim_relative:
                  id: ${light_id}
                  relative_brightness: !lambda 'return (${dim_step} * -1) / 100.0;'
                  transition_length: 0 ms
            else:
              - script.execute:
                  id: feedback_blink
                  condition: !lambda 'return id(${light_id}).get_current_effect_index() > 0;'
              - script.execute:
                  id: walk_effects
                  forward: false



binary_sensor:
  - platform: gpio
    id: ${rotary_encoder_btn_id}
    name: "Knob button"
    internal: true
    pin:
      number: ${re_btn_pin}
      inverted: true
      ignore_strapping_warning: true
    entity_category: diagnostic
    use_interrupt: true
    interrupt_type: ANY
    filters:
      - delayed_on_off: 10 ms
    on_click:
      min_length: 50 ms
      max_length: 500 ms
      then:
        - light.toggle:
            id: ${light_id}


power_supply:
  - id: ac_live
    pin:
      number: ${relay_pin}
      inverted: false
    enable_time: 100 ms
    keep_on_time: 500 ms
    enable_on_boot: false

output:
  - platform: ac_dimmer
    id: ${ac_dimmer_id}
    gate_pin:
      number: ${gate_pin}
      inverted: yes
    zero_cross_pin:
      number: ${zc_pin}
      inverted: no
      mode:
        input: true
    method: trailing
    init_with_half_cycle: true
    zero_means_zero: true
    min_power: ${minimum_level}
    max_power: 100 %
    power_supply: ac_live

  - platform: ledc
    id: led1
    pin:
      number: ${led_1_pin}
      allow_other_uses: true
    frequency: 200 Hz
  - platform: ledc
    id: led2
    frequency: 200 Hz
    pin:
      number: ${led_2_pin}
      ignore_strapping_warning: true
  - platform: ledc
    id: led3
    frequency: 200 Hz
    pin:
      number: ${led_3_pin}
      ignore_strapping_warning: true


script:
  - id: walk_effects
    parameters:
      forward: bool
    then:
      - light.turn_on:
          id: ${light_id}
          effect: !lambda |-
            size_t const effects_count = id(${light_id}).get_effect_count();
            ESP_LOGV("walk_effects", "effects count: %d\n", effects_count);

            uint32_t effect_ndx = id(${light_id}).get_current_effect_index();
            ESP_LOGV("walk_effects", "effect ndx: %d (%s)\n", effect_ndx, id(${light_id}).get_effect_name_by_index(effect_ndx).c_str());

            if (forward == true) {
              if (effect_ndx < effects_count) {
                effect_ndx += 1;
              }
            } else {
              if (effect_ndx > 0) {
                effect_ndx -= 1;
              }
            }
            ESP_LOGV("walk_effects", "new ndx: %d (%s)\n", effect_ndx, id(${light_id}).get_effect_name_by_index(effect_ndx).c_str());

            return id(${light_id}).get_effect_name_by_index(effect_ndx);

  - id: feedback_blink
    parameters:
      condition: bool
    then:
      - if:
          condition:
            lambda: 'return condition == true;'
          then:
            - light.toggle:
                id: ${feedback_led_id}
                transition_length: 0 s
            - delay: ${feedback_blink_length}
            - light.toggle:
                id: ${feedback_led_id}
                transition_length: 0 s

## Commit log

2025-02-23 Exclude exported ibom
2025-03-31 Add separate gerbers
2025-03-31 Add photos
2026-01-05 Update documentation
2026-01-05 Update photos
2026-01-05 Update design
2026-01-05 Update FW
2026-01-05 Split change and release logs. Modify .gitignore to include all export folders.
2026-01-05 Add chassis logs. Split top plate into variants.
2026-01-05 Change title text to image.
2026-01-05 Add title logo.
2026-01-05 Set LEDDs image width to 50%
    Adjusted image width for better display in README.
2026-01-05 Update table of contents and safety warning formatting
2026-01-05 Fix formatting in repository structure section
2026-01-05 Split chassis in variants.
2026-01-05 Add safety warnings for mains voltage operation
    Added cautionary notes regarding mains voltage safety.
2026-01-05 Revise readme for clarity and formatting updates
    Updated various sections for clarity and consistency, including the table of contents, features, and specifications. Adjusted formatting and links for better readability.
2026-01-06 Add new firmware.
2026-01-06 Add BOMs.
2026-01-07 Add firmware variants.
2026-01-08 Hide dimensions and alignment layers.
2026-01-09 Add link to schematic and PCB in README
    Added a link to view the schematic and PCB online.
2026-01-11 Reformat the release log.
2026-01-11 Add road map.
2026-01-11 Update release log.
2026-01-11 Change badge color to lawngreen in releaselog
    Updated badge color for fabrication result in release log.
2026-01-11 Update ibom, add screenshots.
2026-01-11 Corrections.
2026-01-14 Review.
2026-01-15 Add common.yaml
2026-01-16 Update photos.
2026-01-16 Unknown changes.
2026-01-16 Change enclosure folder structure.
2026-01-16 Update image links and names.
2026-01-16 Correct folder name.
2026-01-16 Photos should be jpegs.
2026-01-16 Reduce images display size.
2026-01-16 Center iBOM preview image.
2026-01-16 Fix included libraries. Arrange schematic notes. Add mechanical parts to schematic.
2026-01-16 Remove duplicate model.
2026-01-16 Export BOM. Fix scripts permissions.
2026-01-18 Update exports.
2026-01-18 Add photos to readme.md.
2026-01-18 Consolidate firmware variants in packages.
2026-01-18 Fix image links in README for PCB front and back
2026-01-21 Add docs.
2026-01-22 Change photo.
2026-01-22 Move effects out of packages.
2026-01-23 Add animations to enclosure parts.
2026-01-25 Move.
2026-01-25 Add animation export. Remove unneeded exports.
2026-01-25 Update images.
2026-01-25 Add photos to readmes.
2026-01-25 Add ESPHome's auto-generated .gitignore.
2026-01-25 V2.0 (#2)
    * **Hardware & Mechanical Design**
    * Updated design files and exports.
    * Split chassis and top plate into variants.
    * Changed enclosure folder structure.
    * Hid alignment/dimension layers; removed duplicate models.
    * Added mechanical parts and notes to schematics.
2026-01-25 Update .gitattributes to modify linguist settings
2026-01-25 Update release log for version 2.0
    Updated release date for version 2.0 and removed old comments.
2026-01-26 Update download link for version 2.0 bundle
2026-02-02 Remove MAC suffix. Change framework to esp-idf.
2026-03-07 Update soldering instructions for optoisolators
    Removed instructions to solder R23 for both optoisolators.
